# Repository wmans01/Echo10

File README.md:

# Echo10
Echo10 is a 11 key macropad (10.57% of the keys of an actual keyboard, hence the name). It uses KMK firmware and maximizes functionality through three layers of toggleable keymaps.

## Features
- Two layer 3D printed case
- Minimalistic design to maximize productivity :))
- 8 degree tilt for ergonomic comfort
- 11 Keys
- Seeed Xiao RP2040 MCU
- Ground planes on both sides and stitched vias

## CAD Model:
Case assembled using 4 M3 bolts, screwed directly into plastic on the four corners of the case. 

The case also has an 8 degree incline for ergonomics

Made and rendered in Autodesk Inventor

## PCB
This is the PCB for the Echo10. It is a two layer PCB with ground planes on both sides and uses via stitching. <br>

###### Designed with KiCAD.

I used MX_V2 for the keyswitch footprints. In retrospect, adding feedback through a display or LED might have been more effective. I also could have been more fancy with the designs on the silkscreen.

## Firmware
This macropad uses [KMK](https://github.com/KMKfw/kmk_firmware) firmware.<br>
The current firmware for this macropad allows for 27 different macros. This includes three layers of 9 macros each, accessible through the two switches at the top of the macropad. Currently, the macros are placeholders and just output text, but I will change them later.

## BOM
- 11x Cherry MX Switches
- 11x DSA Keycaps
- 4x M3x12mm SHCS Bolts
- 1x XIAO RP2040
- 1x Case (2 printed parts)

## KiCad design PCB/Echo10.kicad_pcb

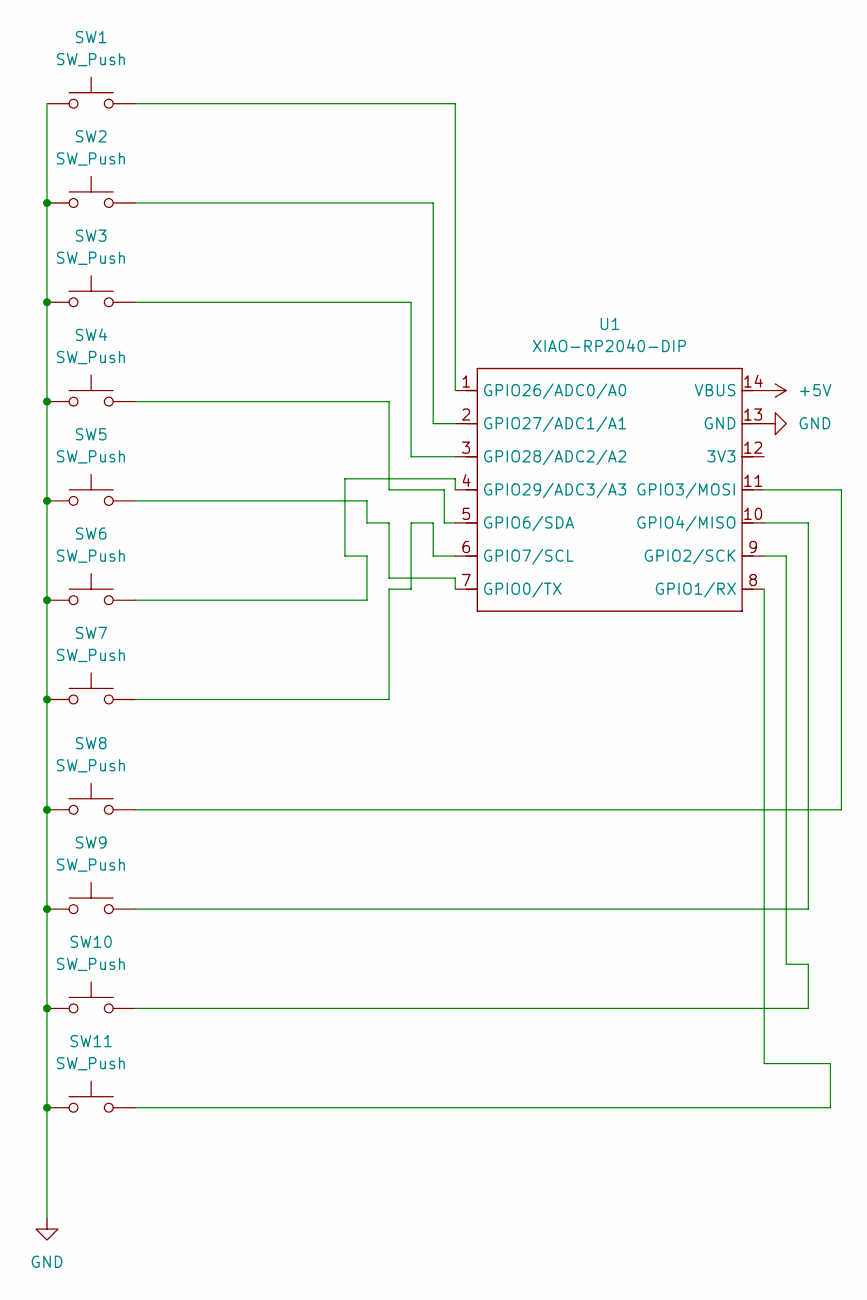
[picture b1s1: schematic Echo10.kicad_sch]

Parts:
SW1, SW2, SW3, SW4, SW5, SW6, SW7, SW8, SW9, SW10, SW11: SW_Push; SW_Cherry_MX_1.00u_PCB
U1: XIAO-RP2040-DIP

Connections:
+5V: U1.14 (VBUS)
GND: SW1.1, SW2.1, SW3.1, SW4.1, SW5.1, SW6.1, SW7.1, SW8.1, SW9.1, SW10.1, SW11.1, U1.13 (GND)
unnamed: SW5.2, U1.7 (GPIO0/TX)
unnamed: SW11.2, U1.8 (GPIO1/RX)
unnamed: SW10.2, U1.9 (GPIO2/SCK)
unnamed: SW8.2, U1.11 (GPIO3/MOSI)
unnamed: SW9.2, U1.10 (GPIO4/MISO)
unnamed: SW4.2, U1.5 (GPIO6/SDA)
unnamed: SW7.2, U1.6 (GPIO7/SCL)
unnamed: SW1.2, U1.1 (GPIO26/ADC0/A0)
unnamed: SW2.2, U1.2 (GPIO27/ADC1/A1)
unnamed: SW3.2, U1.3 (GPIO28/ADC2/A2)
unnamed: SW6.2, U1.4 (GPIO29/ADC3/A3)

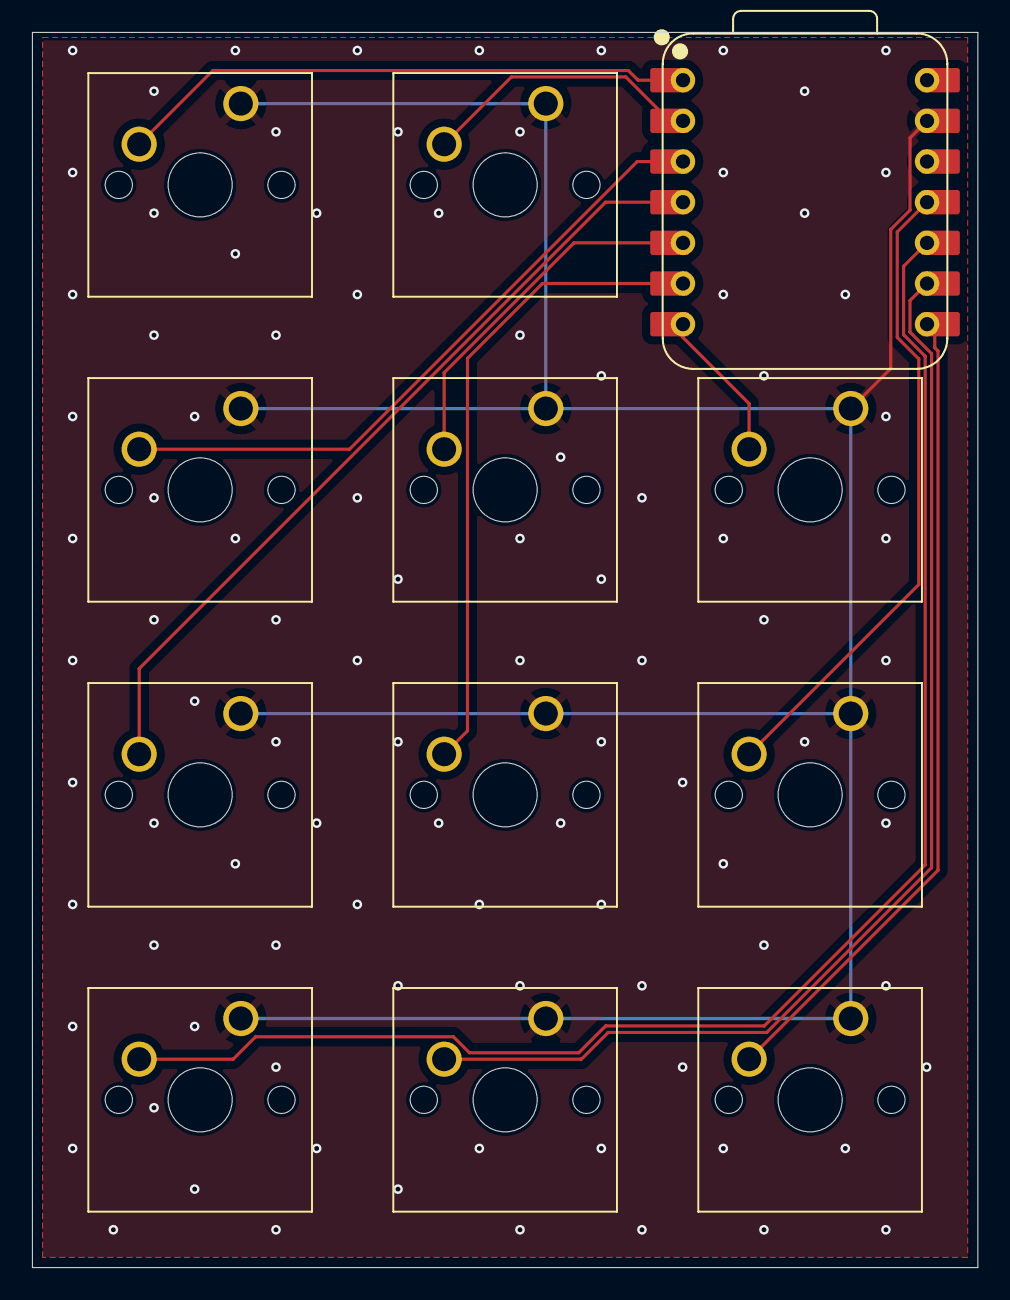
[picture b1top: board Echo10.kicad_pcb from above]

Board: 2 copper layers, 59.1 x 77.2 mm, 12 parts (0 on the bottom side), 12 nets.

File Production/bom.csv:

"Id";"Designator";"Footprint";"Quantity";"Designation";"Supplier and ref";
1;"SW9,SW8,SW5,SW1,SW3,SW7,SW2,SW4,SW6,SW10,SW11";"SW_Cherry_MX_1.00u_PCB";11;"SW_Push";;;
2;"U1";"XIAO-RP2040-DIP";1;"XIAO-RP2040-DIP";;;

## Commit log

2025-06-28 Add PCB and Firmware Files
2025-06-28 Add CAD Files
2025-06-28 Add PCB gerber files
2025-06-28 Add Case STEP Files
2025-06-28 Add Pictures
2025-06-28 Add BOM
2025-06-28 Update File Structure
